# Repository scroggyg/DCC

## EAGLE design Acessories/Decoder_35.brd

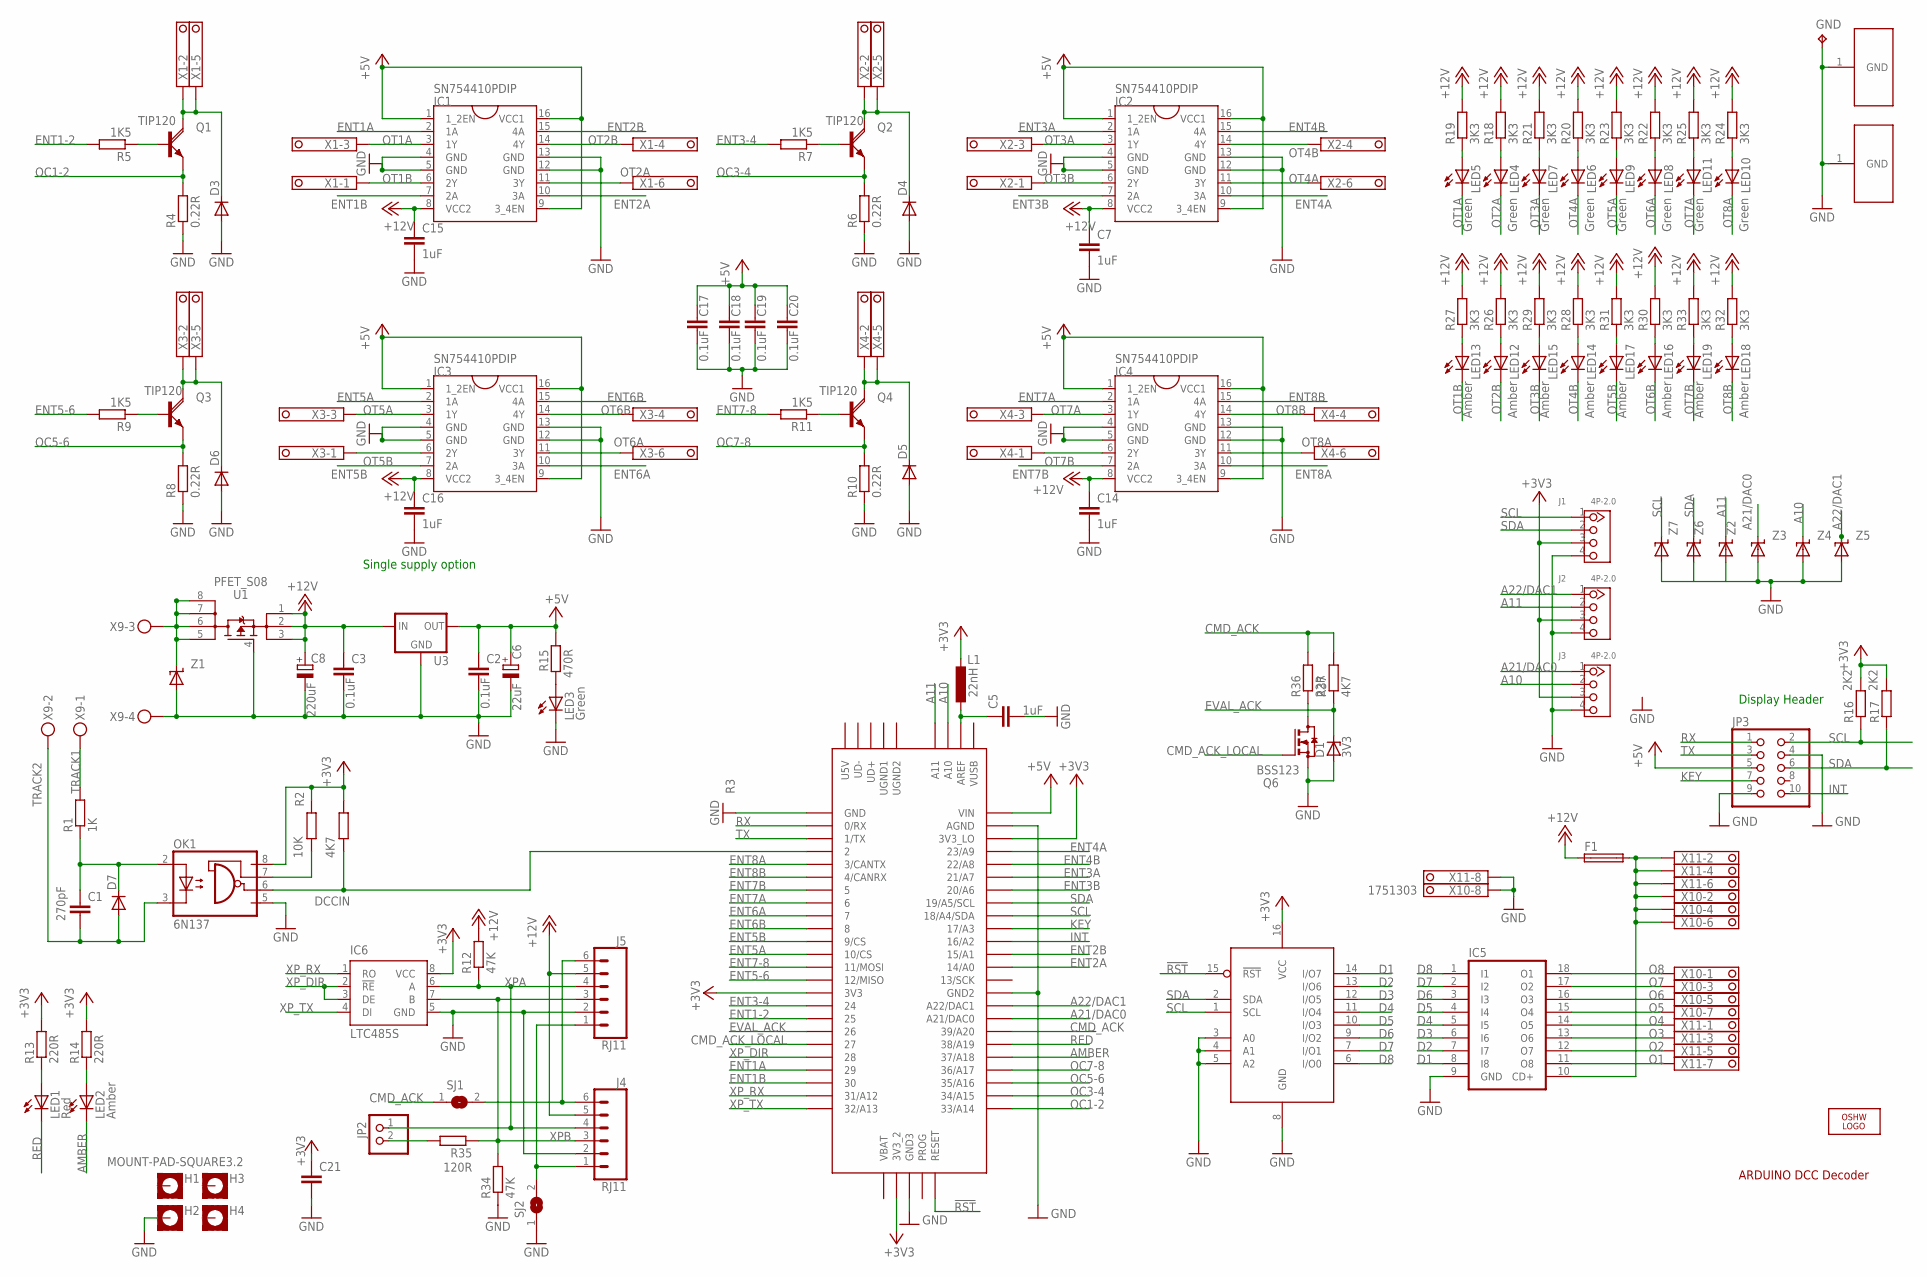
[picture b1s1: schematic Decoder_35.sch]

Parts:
C1: 270pF; C0805
C2, C3, C17, C18, C19, C20: 0.1uF; C0805
C5, C7, C14, C15, C16: 1uF; C0805
C6: 22uF; E2,5-5
C8: 220uF; E5-8,5
C21: C-EUC0805; C0805
D1: 3V3; SOT23
D3, D4, D5, D6, D7: CGRM4002-G; SOD-123_MINI-SMA
F1: SMD_FUSE; 1812
GND: TPB2,54; B2,54
H1, H2, H3, H4: MOUNT-PAD-SQUARE3.2; 3,2-PAD-SQUARE
IC1, IC2, IC3, IC4: SN754410PDIP; DIL16
IC5: ULN2803A; DIL18
IC6: LTC485S; SOIC8
J1, J2, J3: 4P-2.0; HW4-2.0
J4, J5: RJ11; RJ11-6
JP2: PINHD-1X2; 1X02
JP3: PINHD-2X5; 2X05
L1: 22nH; L2012C
LED1: Red; LED3MM
LED2, LED12, LED13, LED14, LED15, LED16, LED17, LED18, LED19: Amber; LED3MM
LED3, LED4, LED5, LED6, LED7, LED8, LED9, LED10, LED11: Green; LED3MM
LOGO1: OSHW_LOGO_6MILX0200-NT; OSHW_6X200_NOTEXT
MT1, MT2: DINC45_MOUNT; DIN_C45
OK1: 6N137; DIL08
Q1, Q2, Q3, Q4: TIP120; TO220AH
Q6: BSS123; SOT23
R1: 1K; R0805
R2: 10K; R0805
R3, R37: 4K7; R0805
R4, R6, R8, R10: 0.22R; R2512
R5, R7, R9, R11: 1K5; R0805
R12, R34: 47K; R0805
R13, R14: 220R; R0805
R15: 470R; R0805
R16, R17: 2K2; R0805
R18, R19, R20, R21, R22, R23, R24, R25, R26, R27, R28, R29, R30, R31, R32, R33: 3K3; R0805
R35: 120R; R0805
R36: 22R; R0805
SJ1, SJ2: SJ
U1: PFET_S08; SO08
U2: PCA9557; S016
U3: V_REG_78XX-TO-220; TO-220-ALT
U$1: TEENSY_3.5/3.6
X1, X2, X3, X4: 1751280
X9: MKDSN1,5/4-5,08
X10, X11: 1751303
Z1: TRANSZORB; SMB
Z2, Z3, Z4, Z5, Z6, Z7: TRANSZORB-SMA; SMA

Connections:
!RST: U2.15 (!RST), U$1.RESET
+3V3: C21.1, IC6.8 (VCC), J1.3, J2.3, J3.3, L1.1, OK1.8 (VCC), R2.2, R3.2, R13.2, R14.2, R16.2, R17.2, U2.16 (VCC), U$1.3V3, U$1.3V3_2, U$1.3V3_LO
+5V: C2.1, C6.+, C17.1, C18.1, C19.1, C20.1, IC1.1 (1_2EN), IC1.9 (3_4EN), IC1.16 (VCC1), IC2.1 (1_2EN), IC2.9 (3_4EN), IC2.16 (VCC1), IC3.1 (1_2EN), IC3.9 (3_4EN), IC3.16 (VCC1), IC4.1 (1_2EN), IC4.9 (3_4EN), IC4.16 (VCC1), JP3.5, R15.2, U3.OUT, U$1.VIN
+12V: C3.1, C7.1, C8.+, C14.1, C15.1, C16.1, F1.1, IC1.8 (VCC2), IC2.8 (VCC2), IC3.8 (VCC2), IC4.8 (VCC2), J4.5, J5.5, R12.2, R18.2, R19.2, R20.2, R21.2, R22.2, R23.2, R24.2, R25.2, R26.2, R27.2, R28.2, R29.2, R30.2, R31.2, R32.2, R33.2, U1.1 (S1), U1.2 (S2), U1.3 (S3), U3.IN
A10: J3.2, U$1.A10, Z4.C
A11: J2.2, U$1.A11, Z2.C
A21/DAC0: J3.1, U$1.21/DAC0 (A21/DAC0), Z3.C
A22/DAC1: J2.1, U$1.A22/DAC1, Z5.C
AMBER: LED2.K (C), U$1.37/A18
CMD_ACK: R36.2, R37.2, SJ1.1, U$1.39/A20
CMD_ACK_LOCAL: Q6.1 (G), U$1.27
D1: IC5.8 (I8), U2.14 (I/O7)
D2: IC5.7 (I7), U2.13 (I/O6)
D3: IC5.6 (I6), U2.12 (I/O5)
D4: IC5.5 (I5), U2.11 (I/O4)
D5: IC5.4 (I4), U2.10 (I/O3)
D6: IC5.3 (I3), U2.9 (I/O2)
D7: IC5.2 (I2), U2.7 (I/O1)
D8: IC5.1 (I1), U2.6 (I/O0)
DCCIN: OK1.6 (VO), R3.1, U$1.2
ENT1-2: R5.2, U$1.25
ENT1A: IC1.2 (1A), U$1.29
ENT1B: IC1.7 (2A), U$1.30
ENT2A: IC1.10 (3A), U$1.14/A0
ENT2B: IC1.15 (4A), U$1.15/A1
ENT3-4: R7.2, U$1.24
ENT3A: IC2.2 (1A), U$1.21/A7
ENT3B: IC2.7 (2A), U$1.20/A6
ENT4A: IC2.10 (3A), U$1.23/A9
ENT4B: IC2.15 (4A), U$1.22/A8
ENT5-6: R9.2, U$1.12/MISO
ENT5A: IC3.2 (1A), U$1.10/CS
ENT5B: IC3.7 (2A), U$1.9/CS
ENT6A: IC3.10 (3A), U$1.7
ENT6B: IC3.15 (4A), U$1.8
ENT7-8: R11.2, U$1.11/MOSI
ENT7A: IC4.2 (1A), U$1.6
ENT7B: IC4.7 (2A), U$1.5
ENT8A: IC4.10 (3A), U$1.3/CANTX
ENT8B: IC4.15 (4A), U$1.4/CANRX
EVAL_ACK: D1.3 (C), R37.1, U$1.26
GND: C2.2, C3.2, C5.2, C6.-, C7.2, C8.-, C14.2, C15.2, C16.2, C17.2, C18.2, C19.2, C20.2, C21.2, D1.1 (A), D3.A, D4.A, D5.A, D6.A, GND.TP, H2.B3,2, IC1.4 (GND), IC1.5 (GND), IC1.12 (GND), IC1.13 (GND), IC2.4 (GND), IC2.5 (GND), IC2.12 (GND), IC2.13 (GND), IC3.4 (GND), IC3.5 (GND), IC3.12 (GND), IC3.13 (GND), IC4.4 (GND), IC4.5 (GND), IC4.12 (GND), IC4.13 (GND), IC5.9 (GND), IC6.5 (GND), J1.4, J2.4, J3.4, J4.2, J5.2, JP3.4, JP3.9, LED3.K (C), MT1.1, MT2.1, OK1.5 (GND), Q6.2 (S), R4.1, R6.1, R8.1, R10.1, R34.1, SJ2.1, U1.4 (G), U2.3 (A0), U2.4 (A1), U2.5 (A2), U2.8 (GND), U3.GND, U$1.AGND, U$1.GND, U$1.GND2, U$1.GND3, X9.4, X10.8, X11.8, Z1.2 (A), Z2.A, Z3.A, Z4.A, Z5.A, Z6.A, Z7.A
INT: JP3.10, U$1.16/A2
KEY: JP3.7, U$1.17/A3
unnamed: C5.1, L1.2, U$1.AREF
unnamed: C1.1, D7.C, OK1.2 (A), R1.1
unnamed: U1.5 (D4), U1.6 (D3), U1.7 (D2), U1.8 (D1), X9.3, Z1.1 (C)
unnamed: OK1.7 (VE), R2.1
unnamed: Q2.B, R7.1
unnamed: Q1.B, R5.1
unnamed: D3.C, Q1.C, X1.2, X1.5
unnamed: LED5.A, R19.1
unnamed: J4.1, J5.1, SJ2.2
unnamed: Q6.3 (D), R36.1
unnamed: D4.C, Q2.C, X2.2, X2.5
unnamed: LED6.A, R20.1
unnamed: LED7.A, R21.1
unnamed: LED8.A, R22.1
unnamed: LED9.A, R23.1
unnamed: LED10.A, R24.1
unnamed: LED11.A, R25.1
unnamed: LED12.A, R26.1
unnamed: Q3.B, R9.1
unnamed: D6.C, Q3.C, X3.2, X3.5
unnamed: LED13.A, R27.1
unnamed: LED14.A, R28.1
unnamed: LED15.A, R29.1
unnamed: LED16.A, R30.1
unnamed: Q4.B, R11.1
unnamed: J4.6, J5.6, SJ1.2
unnamed: D5.C, Q4.C, X4.2, X4.5
unnamed: LED17.A, R31.1
unnamed: LED18.A, R32.1
unnamed: LED19.A, R33.1
unnamed: JP2.2, R35.2
unnamed: F1.2, IC5.10 (CD+), X10.2, X10.4, X10.6, X11.2, X11.4, X11.6
unnamed: LED3.A, R15.1
unnamed: LED1.A, R13.1
unnamed: LED2.A, R14.1
unnamed: LED4.A, R18.1
O1: IC5.11 (O8), X11.7
O2: IC5.12 (O7), X11.5
O3: IC5.13 (O6), X11.3
O4: IC5.14 (O5), X11.1
O5: IC5.15 (O4), X10.7
O6: IC5.16 (O3), X10.5
O7: IC5.17 (O2), X10.3
O8: IC5.18 (O1), X10.1
OC1-2: Q1.E, R4.2, U$1.33/A14
OC3-4: Q2.E, R6.2, U$1.34/A15
OC5-6: Q3.E, R8.2, U$1.35/A16
OC7-8: Q4.E, R10.2, U$1.36/A17
OT1A: IC1.3 (1Y), LED5.K (C), X1.3
OT1B: IC1.6 (2Y), LED13.K (C), X1.1
OT2A: IC1.11 (3Y), LED4.K (C), X1.6
OT2B: IC1.14 (4Y), LED12.K (C), X1.4
OT3A: IC2.3 (1Y), LED7.K (C), X2.3
OT3B: IC2.6 (2Y), LED15.K (C), X2.1
OT4A: IC2.11 (3Y), LED6.K (C), X2.6
OT4B: IC2.14 (4Y), LED14.K (C), X2.4
OT5A: IC3.3 (1Y), LED9.K (C), X3.3
OT5B: IC3.6 (2Y), LED17.K (C), X3.1
OT6A: IC3.11 (3Y), LED8.K (C), X3.6
OT6B: IC3.14 (4Y), LED16.K (C), X3.4
OT7A: IC4.3 (1Y), LED11.K (C), X4.3
OT7B: IC4.6 (2Y), LED19.K (C), X4.1
OT8A: IC4.11 (3Y), LED10.K (C), X4.6
OT8B: IC4.14 (4Y), LED18.K (C), X4.4
RED: LED1.K (C), U$1.38/A19
RX: JP3.1, U$1.0/RX
SCL: J1.1, JP3.2, R16.1, U2.1 (SCL), U$1.18/A4/SDA, Z7.C
SDA: J1.2, JP3.6, R17.1, U2.2 (SDA), U$1.19/A5/SCL, Z6.C
TRACK1: R1.2, X9.1
TRACK2: C1.2, D7.A, OK1.3 (C), X9.2
TX: JP3.3, U$1.1/TX
XPA: IC6.6 (A), J4.4, J5.4, JP2.1, R12.1
XPB: IC6.7 (B), J4.3, J5.3, R34.2, R35.1
XP_DIR: IC6.2 (!RE), IC6.3 (DE), U$1.28
XP_RX: IC6.1 (RO), U$1.31/A12
XP_TX: IC6.4 (DI), U$1.32/A13

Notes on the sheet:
ARDUINO DCC Decoder
Single supply option
Display Header

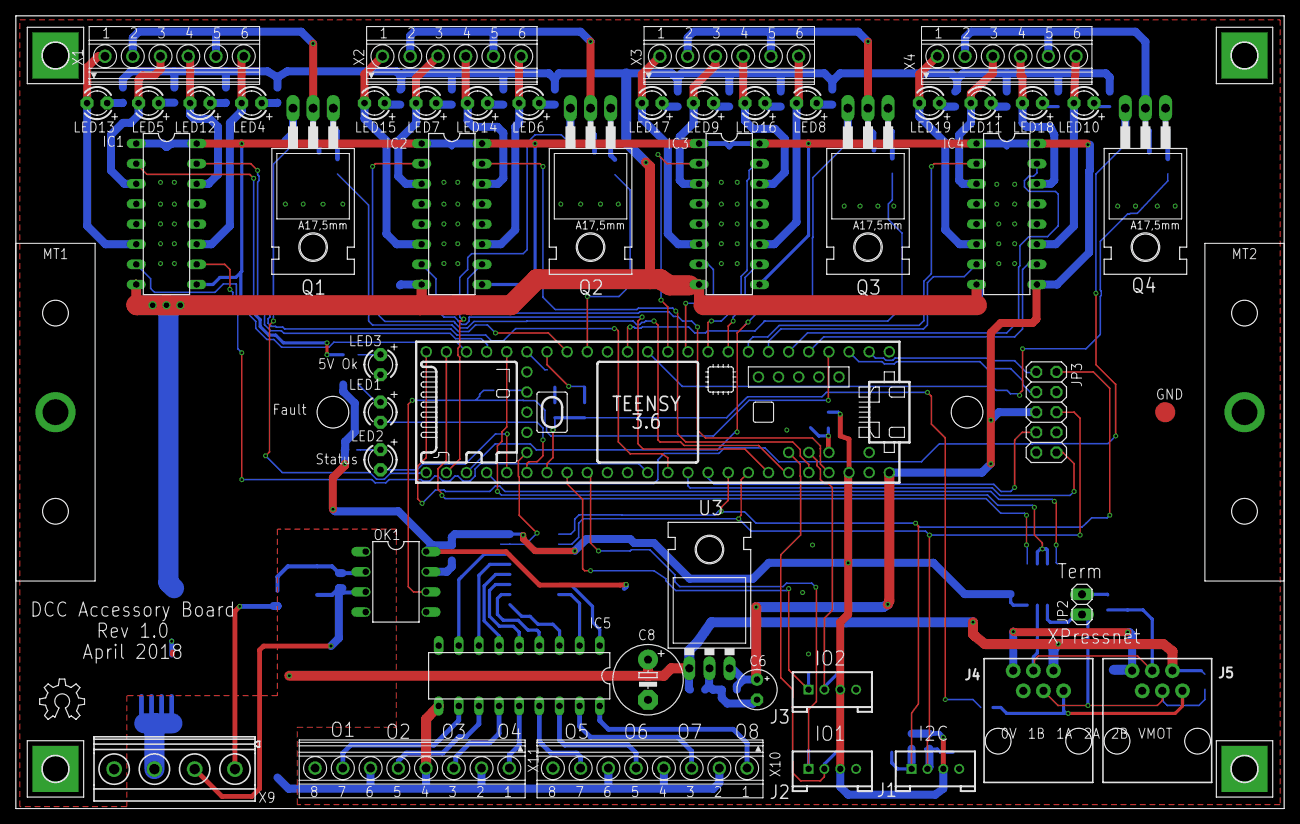
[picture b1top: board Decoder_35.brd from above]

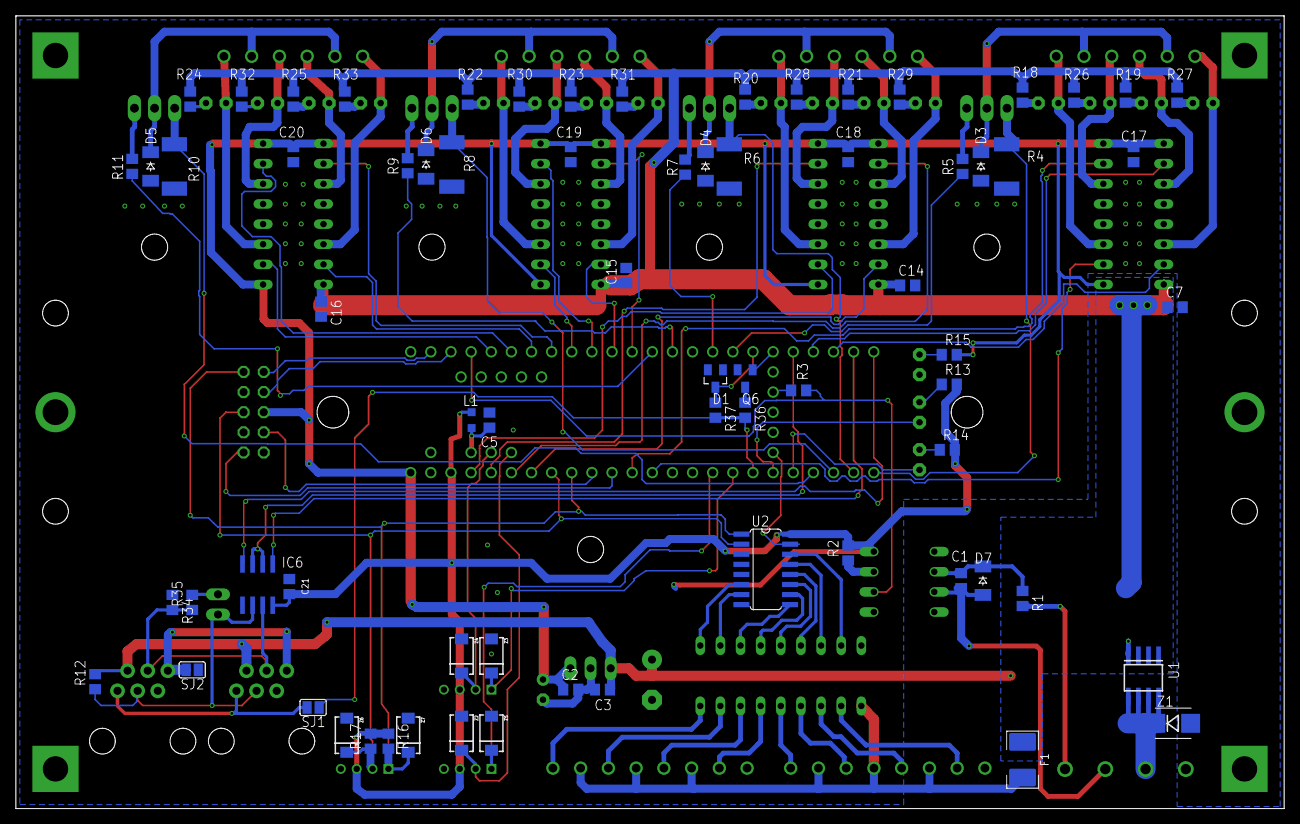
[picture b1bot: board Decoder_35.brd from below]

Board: 2 copper layers, 160.0 x 100.0 mm, 126 parts (71 on the bottom side), 120 nets.

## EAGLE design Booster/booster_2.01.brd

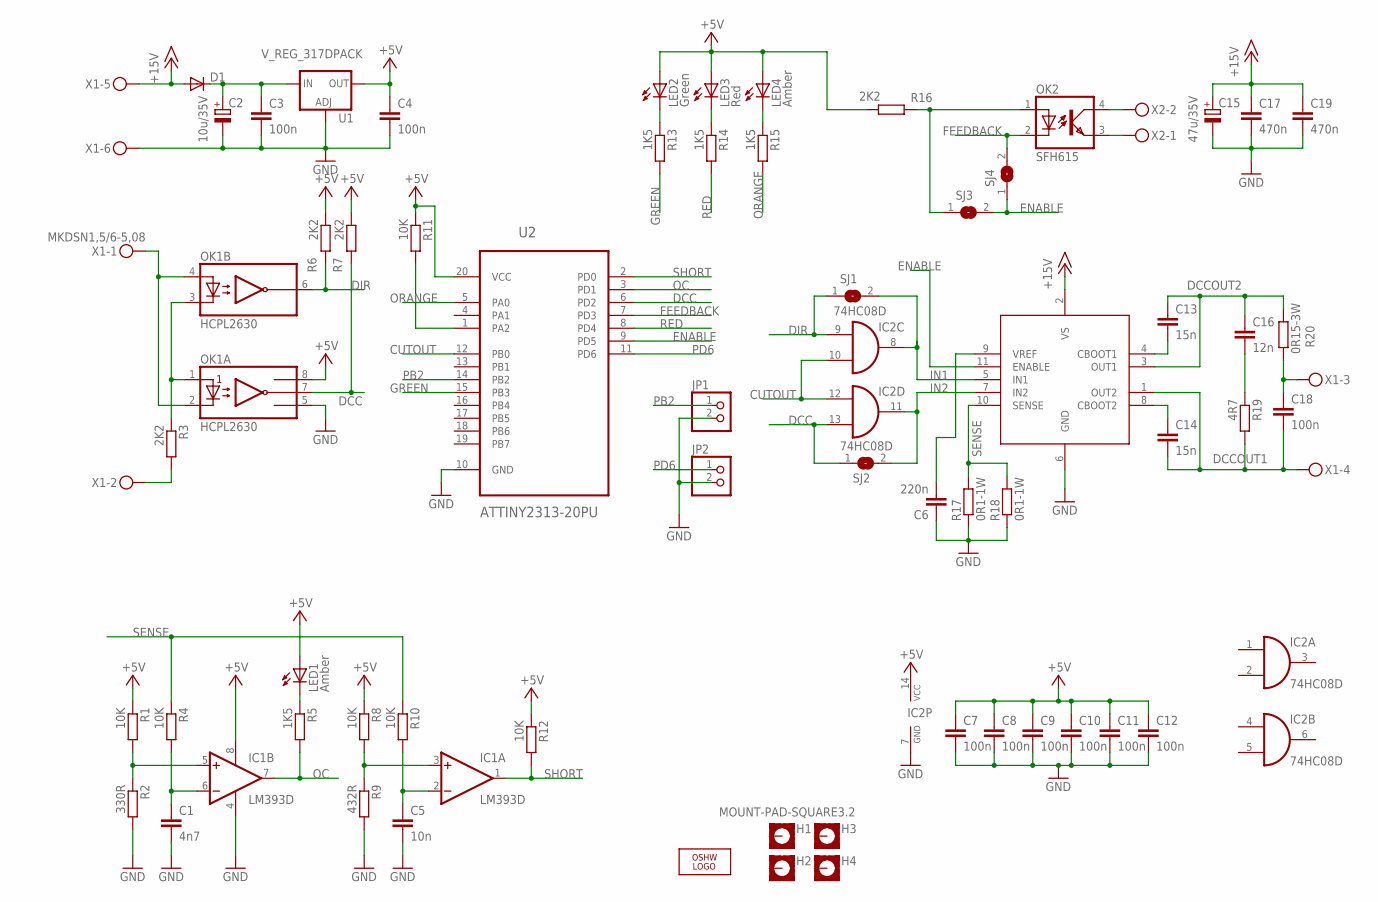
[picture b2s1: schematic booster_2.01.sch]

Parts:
C1: 4n7; C0805
C2: 10u/35V; E2,5-5
C3, C4, C7, C8, C9, C10, C11, C12, C18: 100n; C0805
C5: 10n; C0805
C6: 220n; C0805
C13, C14: 15n; C0805
C15: 47u/35V; E2,5-5
C16: 12n; C0805
C17, C19: 470n; C1812
D1: DIODE-SMB; SMB
H1, H2, H3, H4: MOUNT-PAD-SQUARE3.2; 3,2-PAD-SQUARE
IC1: LM393D; SO08
IC2: 74HC08D; SO14
JP1, JP2: PINHD-1X2; 1X02
LED1, LED4: Amber; LED3MM
LED2: Green; LED3MM
LED3: Red; LED3MM
LOGO1: OSHW_LOGO_6MILX0200-NT; OSHW_6X200_NOTEXT
OK1: HCPL2630; DIL08
OK2: SFH615; DIL04
R1, R4, R8, R10, R11, R12: 10K; R0805
R2: 330R; R0805
R3, R6, R7, R16: 2K2; R0805
R5, R13, R14, R15: 1K5; R0805
R9: 432R; R0805
R17, R18: 0R1-1W; R2512
R19: 4R7; R0805
R20: 0R15-3W; P0817V
SJ1, SJ2, SJ3, SJ4: SJ
U1: V_REG_317DPACK; V-REG_DPACK
U2: ATTINY2313-20PU; DIP254P762X533-20
U3: L6203; ZIP_11
X1: MKDSN1,5/6-5,08
X2: MKDSN1,5/2-5,08

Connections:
+5V: C4.1, C7.1, C8.1, C9.1, C10.1, C11.1, C12.1, IC1.8 (V+), IC2.14 (VCC), LED1.A, LED2.A, LED3.A, LED4.A, OK1.8 (VCC), R1.1, R6.1, R7.1, R8.1, R11.1, R12.1, R16.1, U1.4 (OUT), U2.20 (VCC)
+15V: C15.+, C17.1, C19.1, D1.A, U3.2 (VS), X1.5
CUTOUT: IC2.10 (I1), IC2.12 (I0), U2.12 (PB0)
DCC: IC2.13 (I1), OK1.7 (VO1), R7.2, SJ2.1, U2.6 (PD2)
DCCOUT1: C14.2, C18.2, R19.2, U3.1 (OUT2), X1.4
DCCOUT2: C13.1, C16.1, R20.2, U3.3 (OUT1)
DIR: IC2.9 (I0), OK1.6 (VO2), R6.2, SJ1.1
ENABLE: SJ3.2, SJ4.1, U2.9 (PD5), U3.11 (ENABLE)
FEEDBACK: OK2.2 (C), SJ4.2, U2.7 (PD3)
GND: C1.2, C2.-, C3.2, C4.2, C5.2, C6.1, C7.2, C8.2, C9.2, C10.2, C11.2, C12.2, C15.-, C17.2, C19.2, IC1.4 (V-), IC2.7 (GND), JP1.2, JP2.2, OK1.5 (GND), R2.2, R9.2, R17.1, R18.1, U1.1 (ADJ), U2.10 (GND), U3.6 (GND), X1.6
GREEN: R13.2, U2.15 (PB3)
IN1: IC2.8 (O), SJ1.2, U3.5 (IN1)
IN2: IC2.11 (O), SJ2.2, U3.7 (IN2)
unnamed: OK1.1 (A1), OK1.3 (C2), R3.1
unnamed: OK1.2 (C1), OK1.4 (A2), X1.1
unnamed: R3.2, X1.2
unnamed: R11.2, U2.1 (PA2)
unnamed: IC1.5 (+IN), R1.2, R2.1
unnamed: C1.1, IC1.6 (-IN), R4.2
unnamed: OK2.4 (COL), X2.2
unnamed: IC1.3 (+IN), R8.2, R9.1
unnamed: C5.1, IC1.2 (-IN), R10.2
unnamed: OK2.3 (EMIT), X2.1
unnamed: LED1.K (C), R5.1
unnamed: C2.+, C3.1, D1.C, U1.3 (IN)
unnamed: LED2.K (C), R13.1
unnamed: C18.1, R20.1, X1.3
unnamed: OK2.1 (A), R16.2, SJ3.1
unnamed: LED3.K (C), R14.1
unnamed: LED4.K (C), R15.1
unnamed: C6.2, U3.9 (VREF)
unnamed: C16.2, R19.1
unnamed: C13.2, U3.4 (CBOOT1)
unnamed: C14.1, U3.8 (CBOOT2)
OC: IC1.7 (OUT), R5.2, U2.3 (PD1)
ORANGE: R15.2, U2.5 (PA0)
PB2: JP1.1, U2.14 (PB2)
PD6: JP2.1, U2.11 (PD6)
RED: R14.2, U2.8 (PD4)
SENSE: R4.1, R10.1, R17.2, R18.2, U3.10 (SENSE)
SHORT: IC1.1 (OUT), R12.2, U2.2 (PD0)

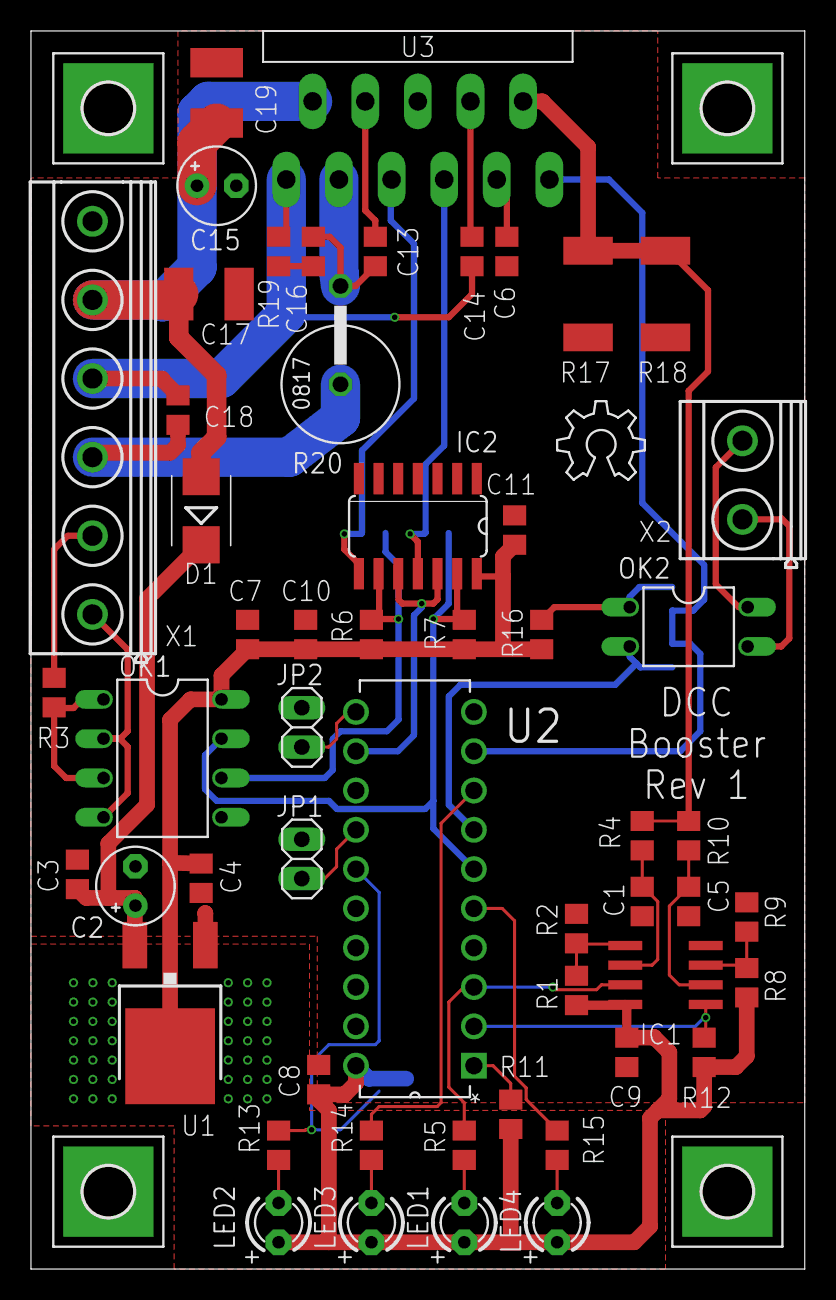
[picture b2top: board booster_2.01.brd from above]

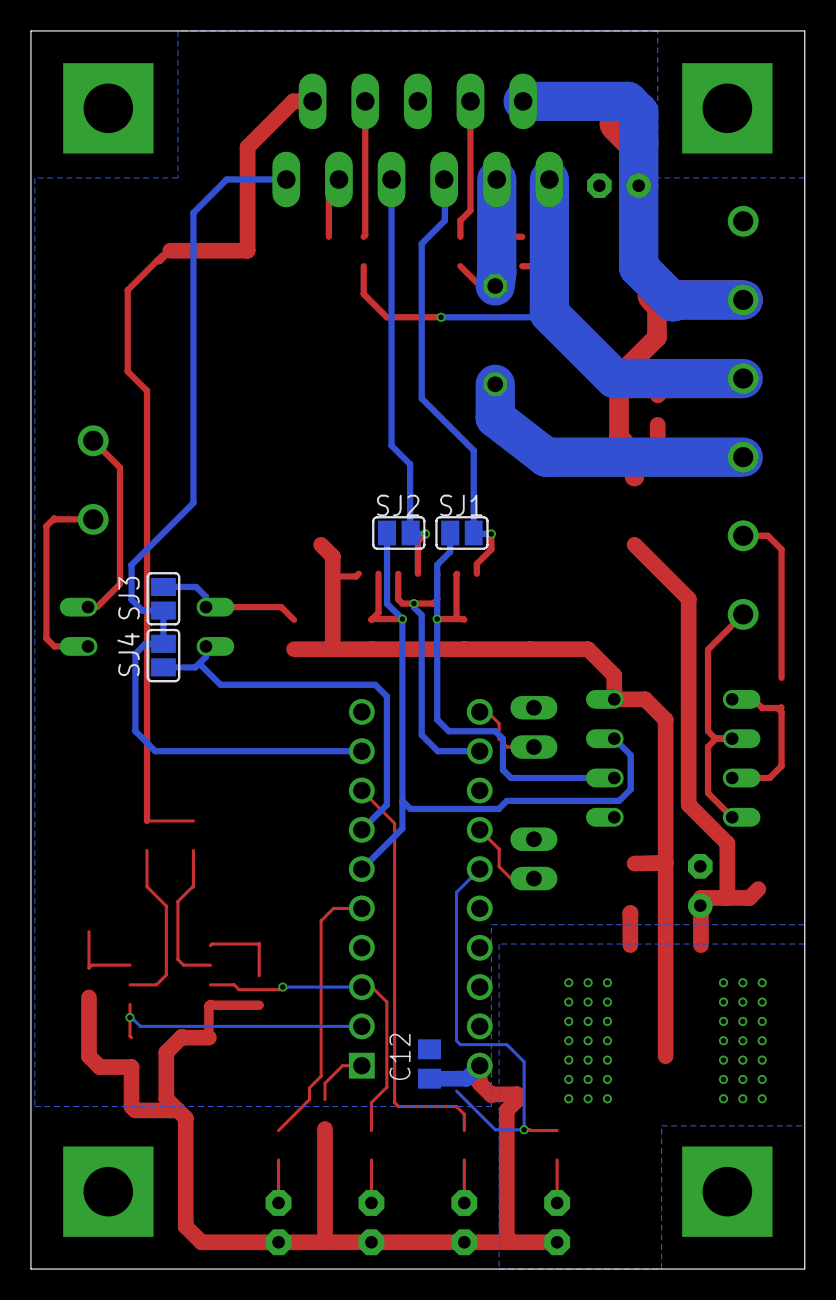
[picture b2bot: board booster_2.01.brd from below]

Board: 2 copper layers, 50.0 x 80.0 mm, 64 parts (5 on the bottom side), 41 nets.

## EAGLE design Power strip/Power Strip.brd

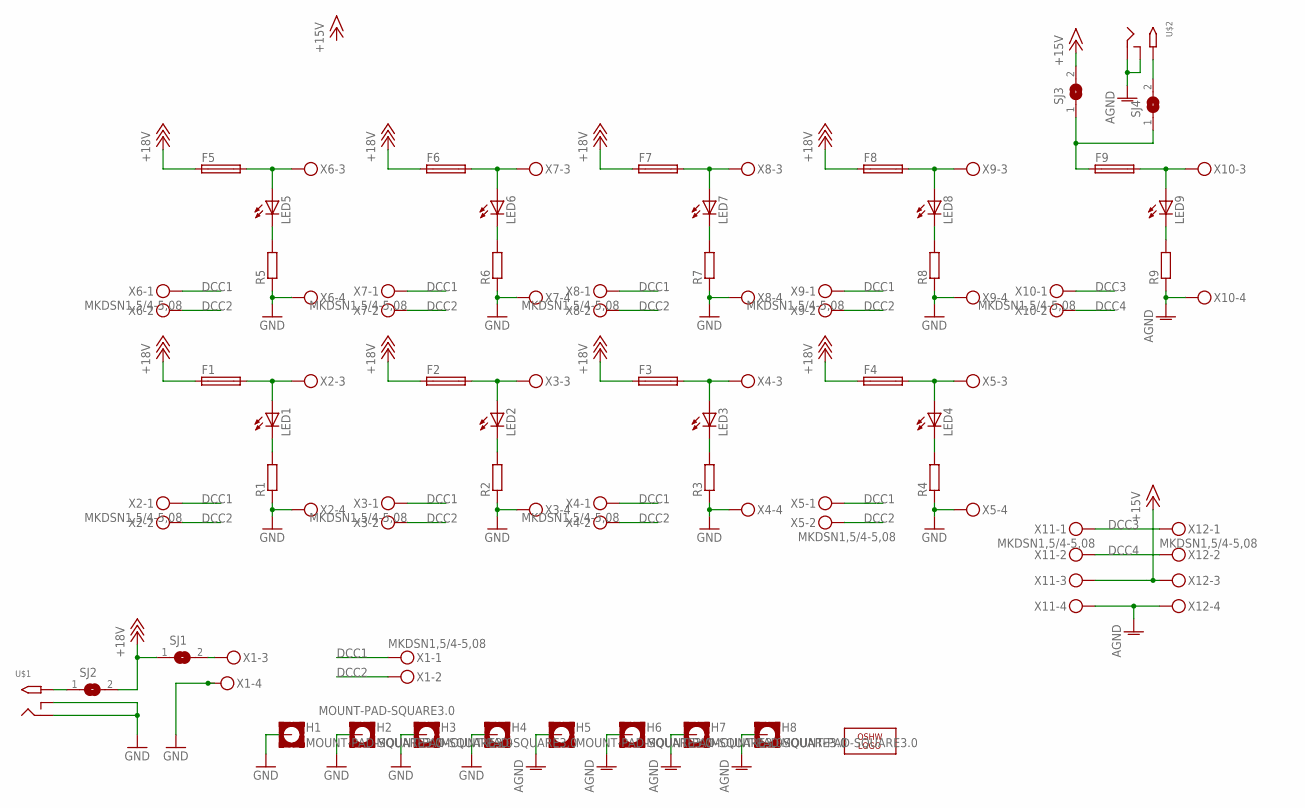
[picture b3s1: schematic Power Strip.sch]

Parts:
F1, F2, F3, F4, F5, F6, F7, F8, F9: TE5
H1, H2, H3, H4, H5, H6, H7, H8: MOUNT-PAD-SQUARE3.0; 3,0-PAD-SQUARE
LED1, LED2, LED3, LED4, LED5, LED6, LED7, LED8, LED9: LED3MM
LOGO1: OSHW_LOGO_6MILX0200-NT; OSHW_6X200_NOTEXT
R1, R2, R3, R4, R5, R6, R7, R8, R9: R-EU_R0805; R0805
SJ1, SJ2, SJ3, SJ4: SJ
U$1, U$2: 2.1MMJACKTHM; PJ-102A
X1, X2, X3, X4, X5, X6, X7, X8, X9, X10, X11, X12: MKDSN1,5/4-5,08

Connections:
+15V: SJ3.2, X11.3, X12.3
+18V: F1.1, F2.1, F3.1, F4.1, F5.1, F6.1, F7.1, F8.1, SJ1.1, SJ2.2
AGND: H5.B3,0, H6.B3,0, H7.B3,0, H8.B3,0, R9.1, U$2.RING, U$2.RING_SW, X10.4, X11.4, X12.4
DCC1: X1.1, X2.1, X3.1, X4.1, X5.1, X6.1, X7.1, X8.1, X9.1
DCC2: X1.2, X2.2, X3.2, X4.2, X5.2, X6.2, X7.2, X8.2, X9.2
DCC3: X10.1, X11.1, X12.1
DCC4: X10.2, X11.2, X12.2
GND: H1.B3,0, H2.B3,0, H3.B3,0, H4.B3,0, R1.1, R2.1, R3.1, R4.1, R5.1, R6.1, R7.1, R8.1, U$1.RING, U$1.RING_SW, X1.4, X2.4, X3.4, X4.4, X5.4, X6.4, X7.4, X8.4, X9.4
unnamed: LED1.K (C), R1.2
unnamed: F1.2, LED1.A, X2.3
unnamed: LED2.K (C), R2.2
unnamed: F2.2, LED2.A, X3.3
unnamed: LED3.K (C), R3.2
unnamed: F3.2, LED3.A, X4.3
unnamed: LED4.K (C), R4.2
unnamed: F4.2, LED4.A, X5.3
unnamed: LED5.K (C), R5.2
unnamed: F5.2, LED5.A, X6.3
unnamed: LED6.K (C), R6.2
unnamed: F6.2, LED6.A, X7.3
unnamed: LED7.K (C), R7.2
unnamed: F7.2, LED7.A, X8.3
unnamed: LED8.K (C), R8.2
unnamed: F8.2, LED8.A, X9.3
unnamed: SJ1.2, X1.3
unnamed: SJ2.1, U$1.TIP
unnamed: LED9.K (C), R9.2
unnamed: F9.2, LED9.A, X10.3
unnamed: F9.1, SJ3.1, SJ4.1
unnamed: SJ4.2, U$2.TIP

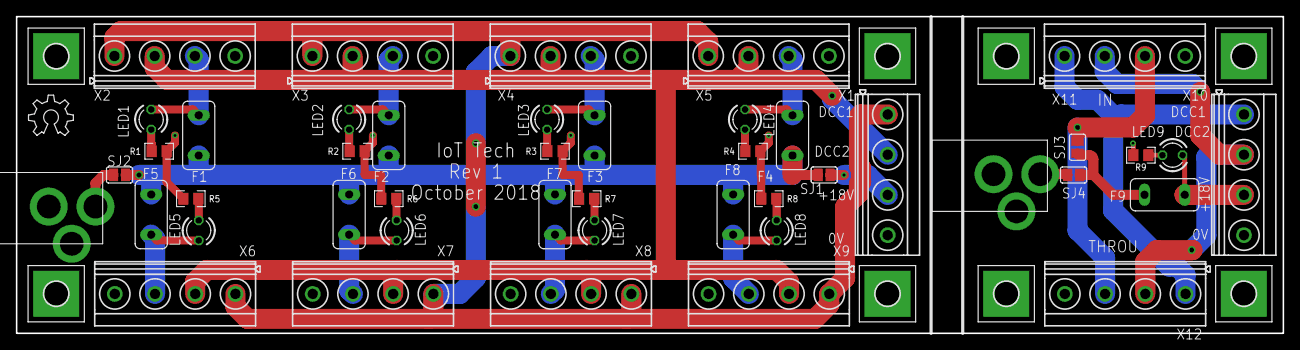
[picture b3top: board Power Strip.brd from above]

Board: 2 copper layers, 160.0 x 40.0 mm, 54 parts (0 on the bottom side), 30 nets.

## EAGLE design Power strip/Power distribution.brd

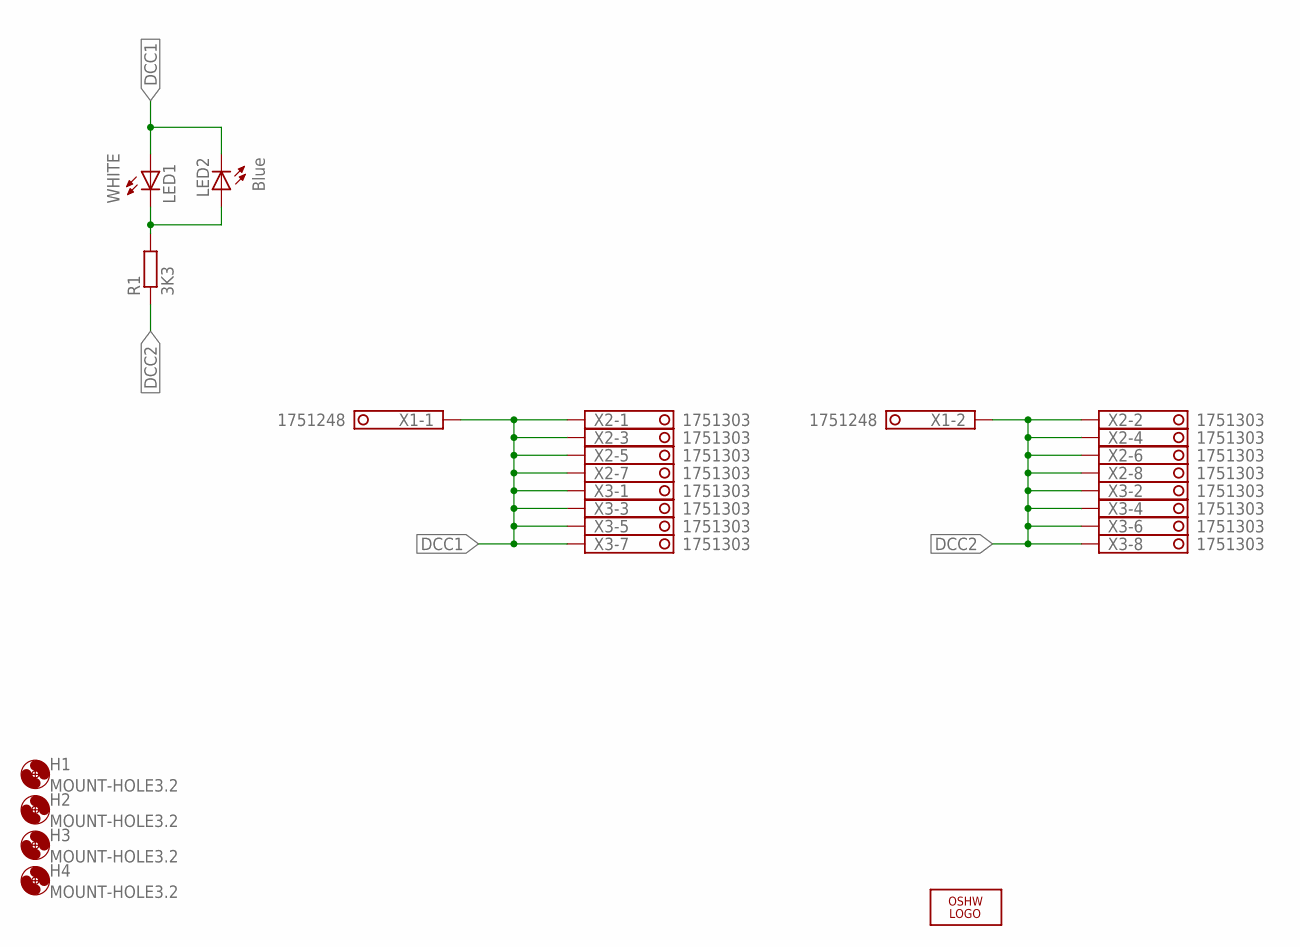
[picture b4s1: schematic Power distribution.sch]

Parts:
H1, H2, H3, H4: MOUNT-HOLE3.2; 3,2
LED1: WHITE; LED3MM
LED2: Blue; LED3MM
LOGO1: OSHW_LOGO_6MILX0200-NT; OSHW_6X200_NOTEXT
R1: 3K3; R0805
X1: 1751248
X2, X3: 1751303

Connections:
DCC1: LED1.A, LED2.K (C), X1.1, X2.1, X2.3, X2.5, X2.7, X3.1, X3.3, X3.5, X3.7
DCC2: R1.1, X1.2, X2.2, X2.4, X2.6, X2.8, X3.2, X3.4, X3.6, X3.8
unnamed: LED1.K (C), LED2.A, R1.2

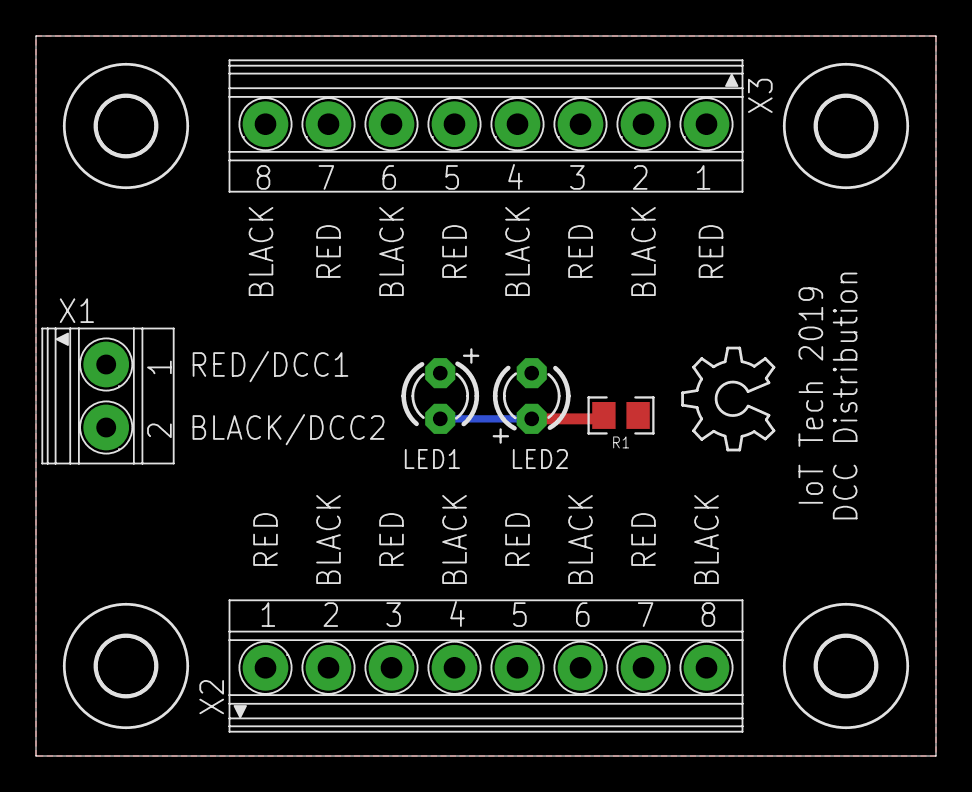
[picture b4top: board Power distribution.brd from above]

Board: 2 copper layers, 50.0 x 40.0 mm, 11 parts (0 on the bottom side), 3 nets.

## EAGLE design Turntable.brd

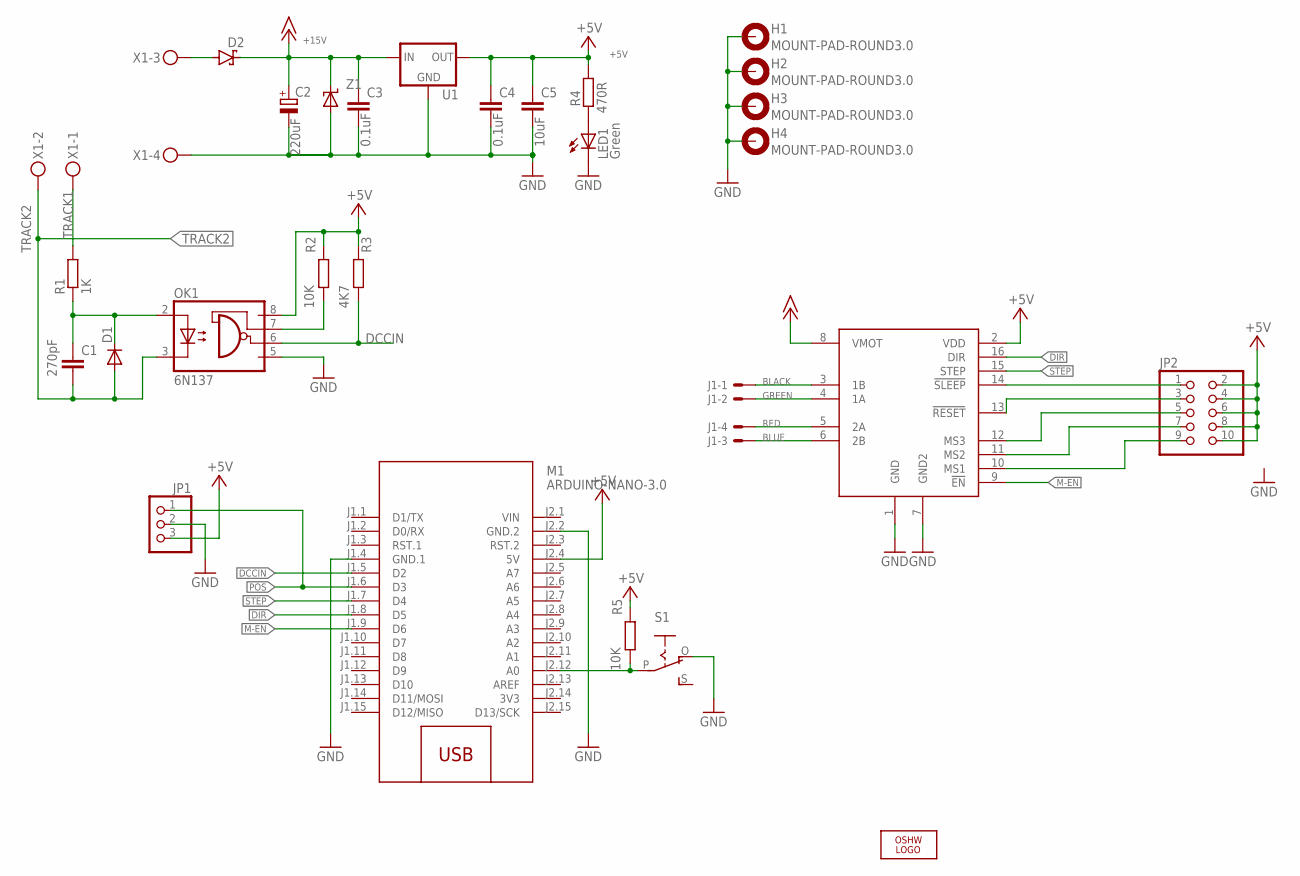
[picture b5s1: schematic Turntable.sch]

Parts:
C1: 270pF; C0805
C2: 220uF; E7,5-16
C3, C4: 0.1uF; C0805
C5: 10uF; C0805
D1: CGRM4002-G; SOD-123_MINI-SMA
D2: SCHOTTKY-DIODESMD; SMB
H1, H2, H3, H4: MOUNT-PAD-ROUND3.0; 3,0-PAD
J1: HEADER4
JP1: PINHD-1X3; 1X03
JP2: PINHD-2X5; 2X05
LED1: Green; LED3MM
LOGO1: OSHW_LOGO_6MILX0200-NT; OSHW_6X200_NOTEXT
M1: ARDUINO-NANO-3.0
OK1: 6N137; DIL08
R1: 1K; R0805
R2, R5: 10K; R0805
R3: 4K7; R0805
R4: 470R; R0805
S1: EG1218S; EG1218
U1: V_REG_78XX-TO-220; TO-220-ALT
U2: A4988; POLOLUA4988
X1: MKDSN1,5/4-5,08
Z1: TRANSZORB; SMB

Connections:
3V3: M1.J2.14 (3V3)
+5V: C4.1, C5.1, JP1.3, JP2.2, JP2.4, JP2.6, JP2.8, JP2.10, M1.J2.4 (5V), OK1.8 (VCC), R2.2, R3.2, R4.2, R5.2, U1.OUT, U2.2 (VDD)
+15V: C2.+, C3.1, D2.C, U1.IN, U2.8 (VMOT), Z1.1 (C)
BLACK: J1.1, U2.3 (1B)
BLUE: J1.3, U2.6 (2B)
DCCIN: M1.J1.5 (D2), OK1.6 (VO), R3.1
DIR: M1.J1.8 (D5), U2.16 (DIR)
GND: C2.-, C3.2, C4.2, C5.2, H1.B3,0, H2.B3,0, H3.B3,0, H4.B3,0, JP1.2, LED1.K (C), M1.J1.4 (GND.1), M1.J2.2 (GND.2), OK1.5 (GND), S1.O, U1.GND, U2.1 (GND), U2.7 (GND2), X1.4, Z1.2 (A)
GREEN: J1.2, U2.4 (1A)
LEARN: M1.J2.12 (A0), R5.1, S1.P
M-EN: M1.J1.9 (D6), U2.9 (!EN)
unnamed: D2.A, X1.3
unnamed: C1.1, D1.C, OK1.2 (A), R1.1
unnamed: OK1.7 (VE), R2.1
unnamed: JP2.9, U2.10 (MS1)
unnamed: JP2.1, U2.14 (!SLEEP)
unnamed: JP2.3, U2.13 (!RESET)
unnamed: JP2.5, U2.12 (MS3)
unnamed: JP2.7, U2.11 (MS2)
unnamed: LED1.A, R4.1
POS: JP1.1, M1.J1.6 (D3)
RED: J1.4, U2.5 (2A)
STEP: M1.J1.7 (D4), U2.15 (STEP)
TRACK1: R1.2, X1.1
TRACK2: C1.2, D1.A, OK1.3 (C), X1.2
VIN: M1.J2.1 (VIN)

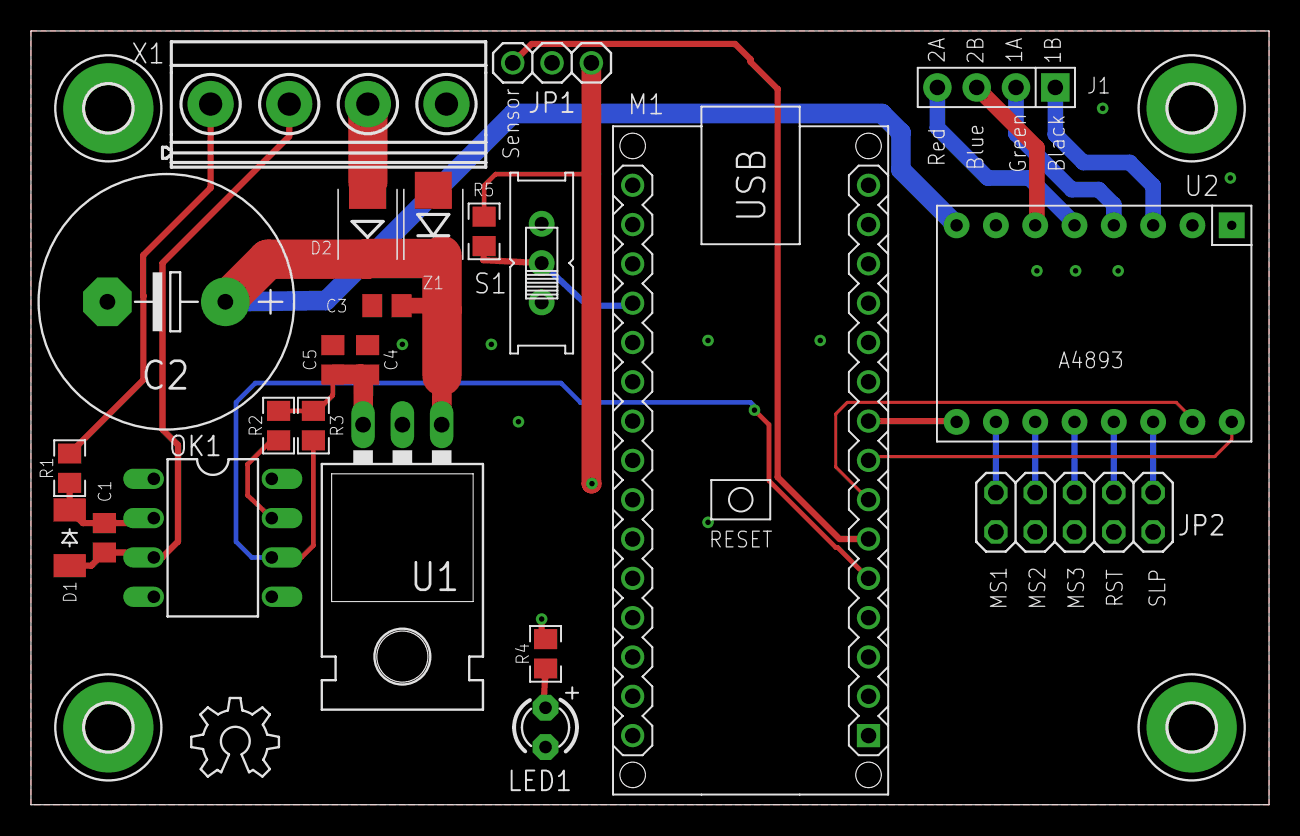
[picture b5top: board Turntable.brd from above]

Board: 2 copper layers, 80.0 x 50.0 mm, 28 parts (0 on the bottom side), 24 nets.

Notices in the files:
parts and their libraries:
SparkFun-IC-Power: Licensing: Creative Commons ShareAlike 4.0 International - https://creativecommons.org/licenses/by-sa/4.0
diy-modules: Released under the Creative Commons Attribution 4.0 International License: http://creativecommons.org/licenses/by/4.0
